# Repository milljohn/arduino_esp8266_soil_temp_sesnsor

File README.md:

# Arduino Soil Temperature Sensor

This began as a project for EE300 at New Mexico State University for the Fall 2018 semester. The scope of the project was to customize an existing Arduino based project using SMT components.

V0.1: Original design presented. Made use of an analog temperature sensor, LMT88. This worked correctly, however it required a voltage divider because the analog input on the ESP8266 is only 1V tolerant. This meant that there was a constant drain on the battery, even when the MCU was in deep sleep.

V0.2 Updated design

## Overview

- MCU: [ESP8266](https://www.espressif.com/sites/default/files/documentation/0a-esp8266ex_datasheet_en.pdf)
  - Minimal ciruitry to program and run
  - No on board USB to UART
- Sensor(s):
  - V0.1: [LMT88](https://www.ti.com/lit/ds/symlink/lmt88.pdf), other 3 pin analog sensor should work
  - V0.2: [DS18b20](https://datasheets.maximintegrated.com/en/ds/DS18B20.pdf)

## Schematics

The Scematics are in the pcb directory. Current version is Soil Temp V0.02. The main difference between V0.01 and v0.02 is the temperature sensor.

## Programming

The program PostDataToGooleSheets takes a temp reading every hour, posts to Google Sheets, and then goes into deep sleep.

NOTE: Google sent me warnings about the sheet because it was public and eventually disabled public access.

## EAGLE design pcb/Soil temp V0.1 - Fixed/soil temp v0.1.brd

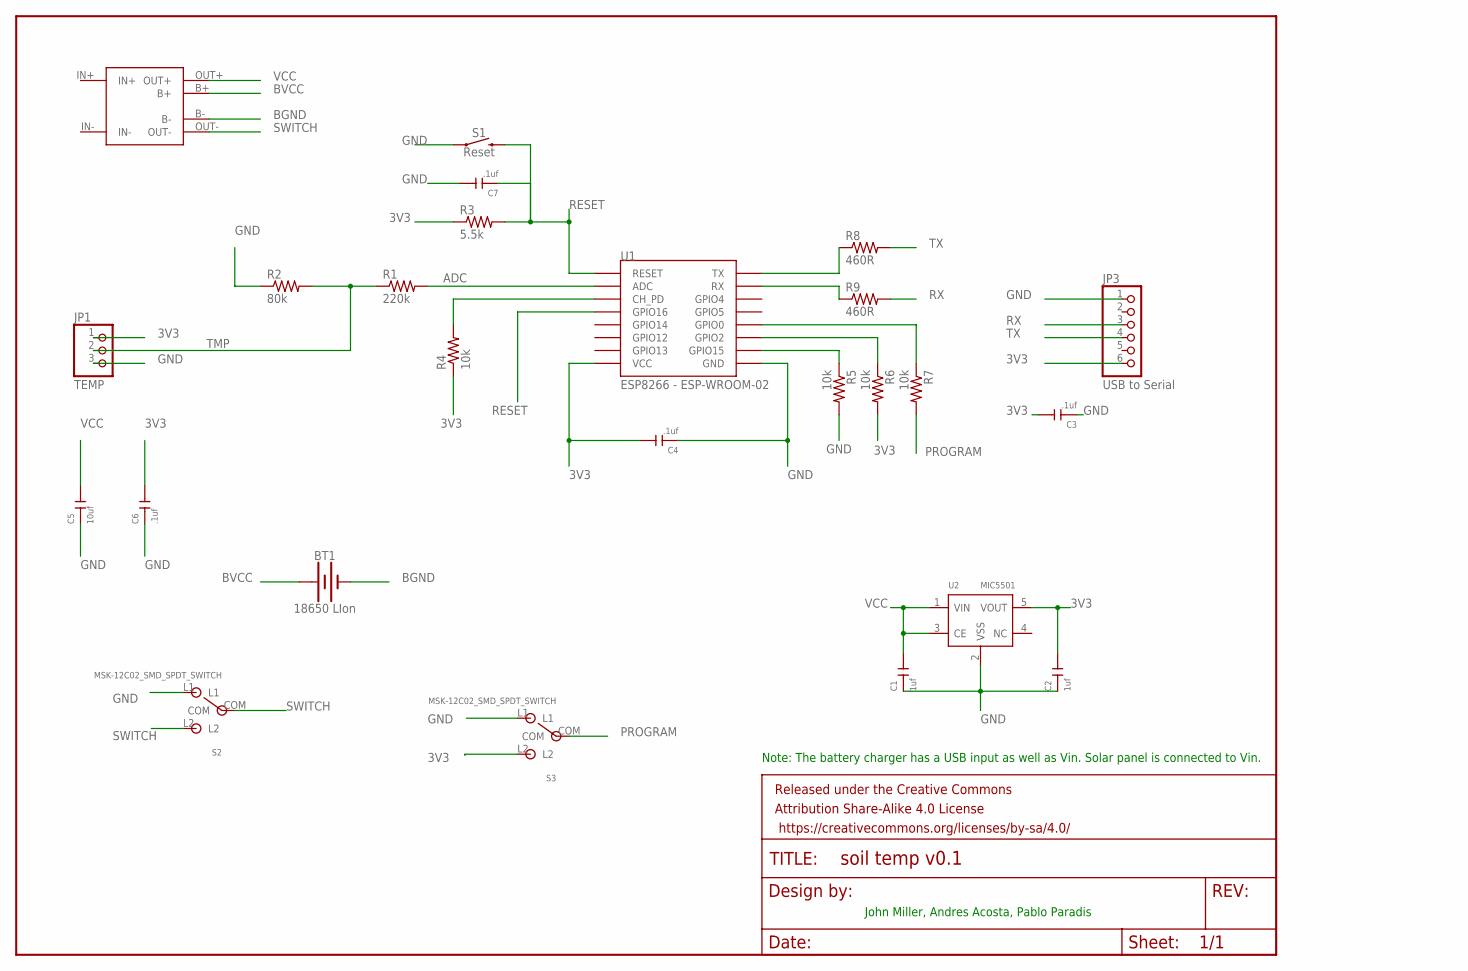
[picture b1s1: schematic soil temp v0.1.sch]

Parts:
BT1: 18650 LIon; BATTERY_18650-HOLDER
C1, C2: 1uf; C0805
C3, C4, C6, C7: .1uf; C0805
C5: 10uf; C0805
FRAME1: FRAME-LETTERNO_PACKAGE; DUMMY
JP1: TEMP; 1X03
JP3: USB to Serial; 1X06/90
R1: 220k; R0805
R2: 80k; R0805
R3: 5.5k; R0805
R4, R5, R6, R7: 10k; R0805
R8, R9: 460R; R0805
S1: Reset; TACTILE_SWITCH_SMD_6.2MM_TALL
S2, S3: MSK-12C02_SMD_SPDT_SWITCH; MSK-12C02
U1: ESP8266 - ESP-WROOM-02; ESP12
U2: MIC5501; SOT-23-5
U3: TP4056-MODULE; TP4056-LITHIUM-PROTECTED-MODULE

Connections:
3V3: C2.2, C3.2, C4.2, C6.2, JP1.1, JP3.6, R3.1, R4.1, R6.2, S3.L2, U1.VCC, U2.5 (VOUT)
ADC: R1.2, U1.ADC
BGND: BT1.GND@1 (-), U3.B-
BVCC: BT1.PWR@1 (+), U3.B+
GND: C1.1, C2.1, C3.1, C4.1, C5.1, C6.1, C7.2, JP1.3, JP3.1, R2.1, R5.2, S1.A2 (1), S2.L1, S3.L1, U1.GND, U2.2 (VSS)
IN+: U3.IN+
IN-: U3.IN-
unnamed: R4.2, U1.CH_PD
unnamed: R5.1, U1.GPIO15
unnamed: R6.1, U1.GPIO2
unnamed: R7.1, U1.GPIO0
PROGRAM: R7.2, S3.COM
R2RX: R9.1, U1.RX
R2TX: R8.1, U1.TX
RESET: C7.1, R3.2, S1.B2 (2), U1.GPIO16, U1.RESET
RX: JP3.3, R9.2
SWITCH: S2.COM, S2.L2, U3.OUT-
TMP: JP1.2, R1.1, R2.2
TX: JP3.4, R8.2
VCC: C1.2, C5.2, U2.1 (VIN), U2.3 (CE), U3.OUT+

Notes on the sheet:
Note: The battery charger has a USB input as well as Vin. Solar panel is connected to Vin.
John Miller, Andres Acosta, Pablo Paradis

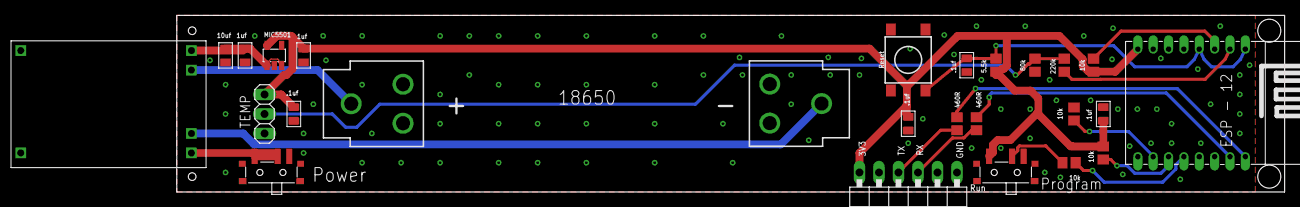
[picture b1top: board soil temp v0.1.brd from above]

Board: 2 copper layers, 144.3 x 23.0 mm, 26 parts (0 on the bottom side), 18 nets.

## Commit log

2020-05-03 first
2020-05-04 PCB and Program Added

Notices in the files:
parts and their libraries:
SparkFun-Aesthetics: Licensing: Creative Commons ShareAlike 4.0 International - https://creativecommons.org/licenses/by-sa/4.0
SparkFun-Aesthetics: Released under the Creative Commons Attribution Share-Alike 4.0 License
SparkFun-Aesthetics: https://creativecommons.org/licenses/by-sa/4.0
